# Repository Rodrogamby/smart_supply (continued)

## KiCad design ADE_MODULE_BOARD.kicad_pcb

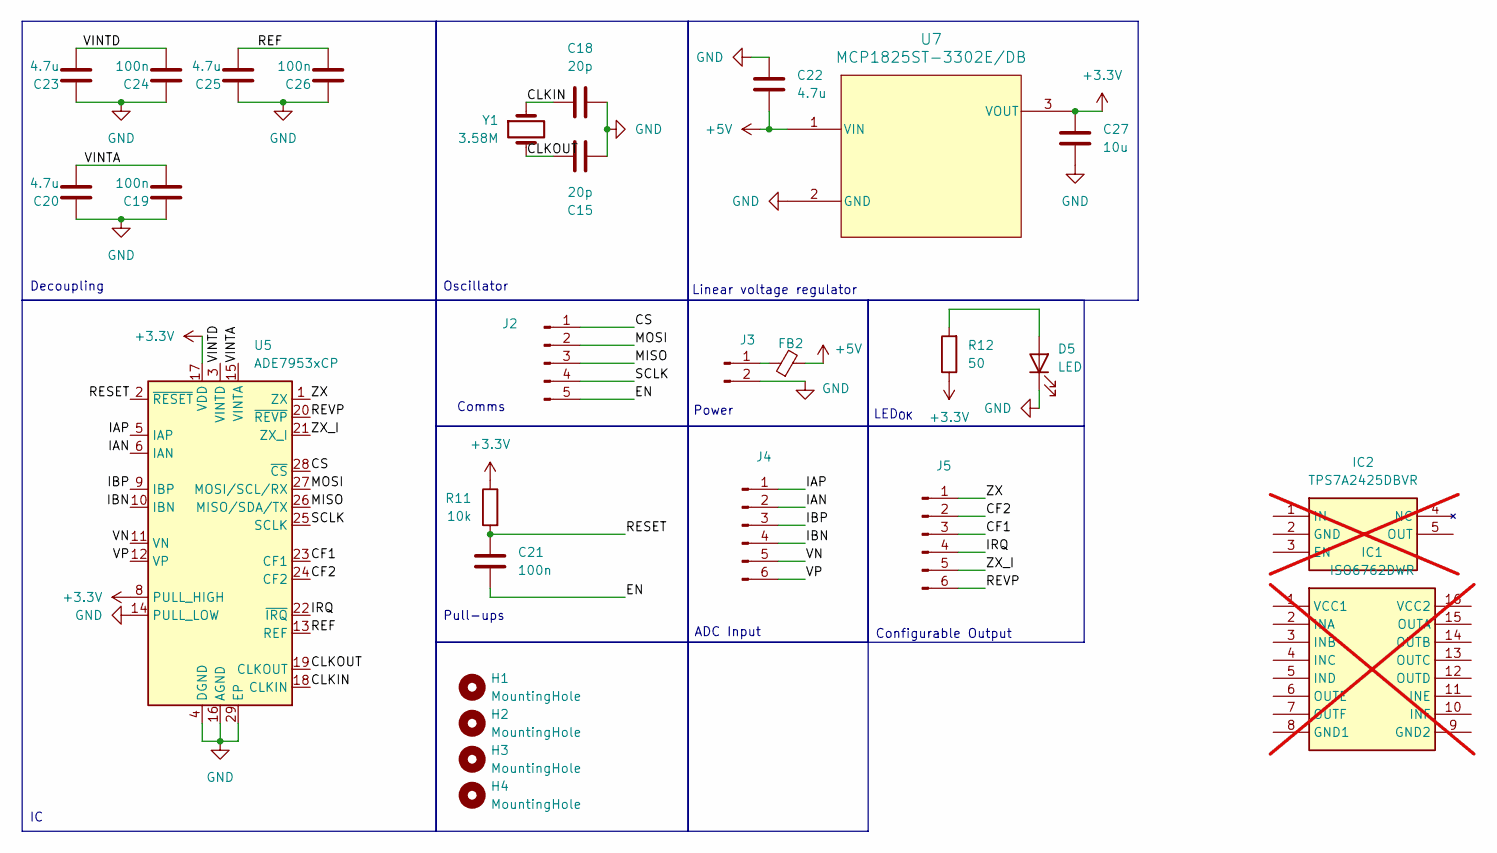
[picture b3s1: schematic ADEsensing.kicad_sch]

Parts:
C15, C18: 20p; C_0603_1608Metric; MPN C165732
C19, C21, C24, C26: 100n; C_0603_1608Metric; MPN C1590
C20, C22, C23, C25: 4.7u; C_0805_2012Metric; MPN C1779
C27: 10u; C_0805_2012Metric; MPN C15850
D5: LED; LED_0805_2012Metric; MPN C2986046
FB2: FerriteBead_Small; L_0805_2012Metric; MPN C1015
H1, H2, H3, H4: MountingHole; MountingHole_2.7mm_M2.5
IC1: ISO6762DWR; SOIC127P1030X265-16N; Mouser Part Number 595-ISO6762DWR; not fitted
IC2: TPS7A2425DBVR; SOT95P280X145-5N; Mouser Part Number 595-TPS7A2425DBVR; not fitted
J2: Conn_01x05_Pin; PinHeader_1x05_P2.54mm_Vertical
J3: Conn_01x02_Pin; PinHeader_1x02_P2.54mm_Vertical
J4, J5: Conn_01x06_Pin; PinHeader_1x06_P2.54mm_Vertical
R11: 10k; R_0805_2012Metric; MPN C17414
R12: 50; R_0805_2012Metric; MPN C55205334
U5: ADE7953xCP; LFCSP-28-1EP_5x5mm_P0.5mm_EP3.14x3.14mm_ThermalVias; MPN C515890
U7: MCP1825ST-3302E/DB; SOT-223-3_TabPin2; MPN C145411
Y1: 3.58M; Crystal_SMD_HC49-SD; MPN C22464956

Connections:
+3.3V: C27.1, R11.1, R12.1, U5.7 (PULL_HIGH), U5.8 (PULL_HIGH), U5.17 (VDD), U7.3 (VOUT)
+5V: C22.2, FB2.2, U7.1 (VIN)
/ADE Module/CF1: J5.3, U5.23 (CF1)
/ADE Module/CF2: J5.2, U5.24 (CF2)
/ADE Module/CLKIN: C18.1, U5.18 (CLKIN), Y1.1
/ADE Module/CLKOUT: C15.2, U5.19 (CLKOUT), Y1.2
/ADE Module/CS: J2.1, U5.28 (~CS)
/ADE Module/EN: C21.2, J2.5
/ADE Module/IAN: J4.2, U5.6 (IAN)
/ADE Module/IAP: J4.1, U5.5 (IAP)
/ADE Module/IBN: J4.4, U5.10 (IBN)
/ADE Module/IBP: J4.3, U5.9 (IBP)
/ADE Module/IRQ: J5.4, U5.22 (~IRQ)
/ADE Module/MISO: J2.3, U5.26 (MISO/SDA/TX)
/ADE Module/MOSI: J2.2, U5.27 (MOSI/SCL/RX)
/ADE Module/REF: C25.2, C26.2, U5.13 (REF)
/ADE Module/RESET: C21.1, R11.2, U5.2 (~RESET)
/ADE Module/REVP: J5.6, U5.20 (~REVP)
/ADE Module/SCLK: J2.4, U5.25 (SCLK)
/ADE Module/VINTA: C19.2, C20.2, U5.15 (VINTA)
/ADE Module/VINTD: C23.2, C24.2, U5.3 (VINTD)
/ADE Module/VN: J4.5, U5.11 (VN)
/ADE Module/VP: J4.6, U5.12 (VP)
/ADE Module/ZX: J5.1, U5.1 (ZX)
/ADE Module/ZX_I: J5.5, U5.21 (ZX_I)
GND: C15.1, C18.2, C19.1, C20.1, C22.1, C23.1, C24.1, C25.1, C26.1, C27.2, D5.1 (K), J3.2, U5.4 (DGND), U5.14 (PULL_LOW), U5.16 (AGND), U5.29 (EP), U7.2 (GND)
unnamed: D5.2 (A), R12.2
unnamed: FB2.1, J3.1

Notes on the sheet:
Configurable Output
Oscillator
Power
Comms
Linear voltage regulator
Pull-ups
LED_{OK}
ADC Input
Decoupling

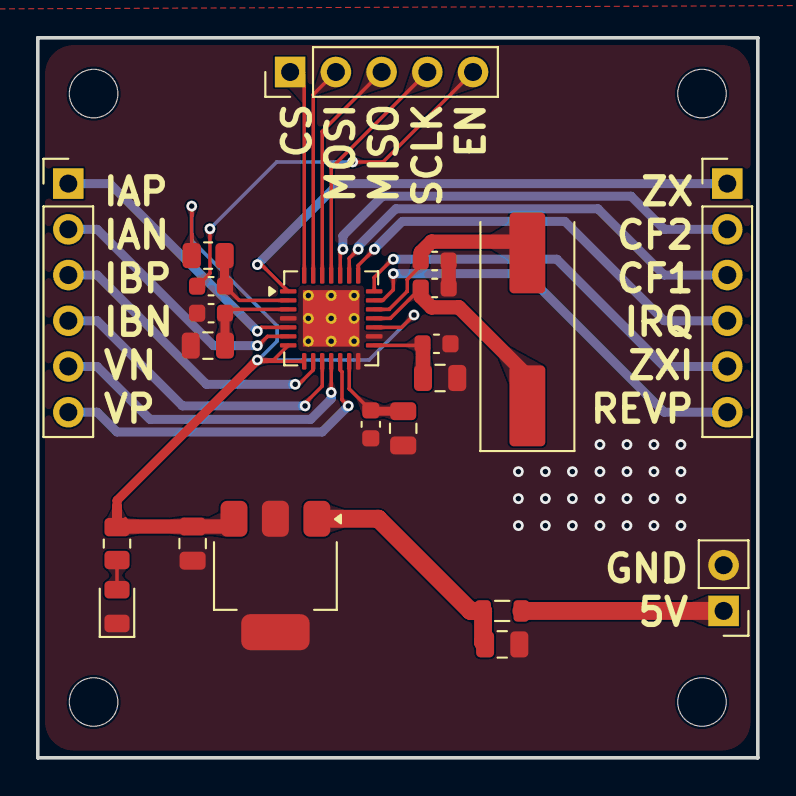
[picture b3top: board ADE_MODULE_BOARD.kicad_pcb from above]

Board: 2 copper layers, 40.0 x 40.0 mm, 26 parts (0 on the bottom side), 28 nets.
